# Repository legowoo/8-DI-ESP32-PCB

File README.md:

# 8-DI-ESP32-PCB
A printed circuit board that enables a ESP32 to interface with digital inputs up to 28VDC.

# Features
- 8 Galvanically isolated inputs
- Pluggable terminal blocks for connecting sensors
- Supports 12 and 24VDC sensors
- ESD protected inputs
- Reverse polarity protection
- Over current protection

# Technical Specification
- ESP32 Input voltage 5-16VDC
- Sensor Input voltage 5-28VDC (with 3/4W input resistors)
- Maximum input current draw 12mA
- Maximum board power draw ~10W

# Schematic

# How to use
- J9: Screw terminal for supplying voltage to the sensors that are connected to the optocouplers. Input voltage range: 5-24VDC
- J10: Screw terminal for supplying voltage to the ESP itself. Input voltage range: 5-12VDC

- D11: Led to indicate the presents/absent of a voltage on the VCC rail (J9).
- D12: Led to indicate the presents/absent of the +3V3 rail (J10).

- JP1: Jumper to connect the VCC to VPP. Used to remove the Galvanic isolation between the sensors and ESP.  
**Only populate this jumper if one voltage source is being used!**
- JP2: Jumper to connect GND1 to GND2. Used to remove the Galvanic isolation between the sensors and ESP.

- J1-J8: Each digital input has its own header connected to the ESP. Pinout from left to right: 1=VCC, 2=GND and 3=GPIO

- SW1: Resart the ESP
- SW2: put the ESP in program mode if the ESP is booting

- J11: Program connector. Connect any +3V3 UART programmer to write a program to the ESP.  
note: the ESP needs to be manualy set to program mode via SW1 and SW2.

# I/O mapping:  
- J1 -> GPIO36
- J2 -> GPIO39
- J3 -> GPIO34
- J4 -> GPIO35
- J5 -> GPIO19
- J6 -> GPIO21
- J7 -> GPIO22
- J8 -> GPIO23

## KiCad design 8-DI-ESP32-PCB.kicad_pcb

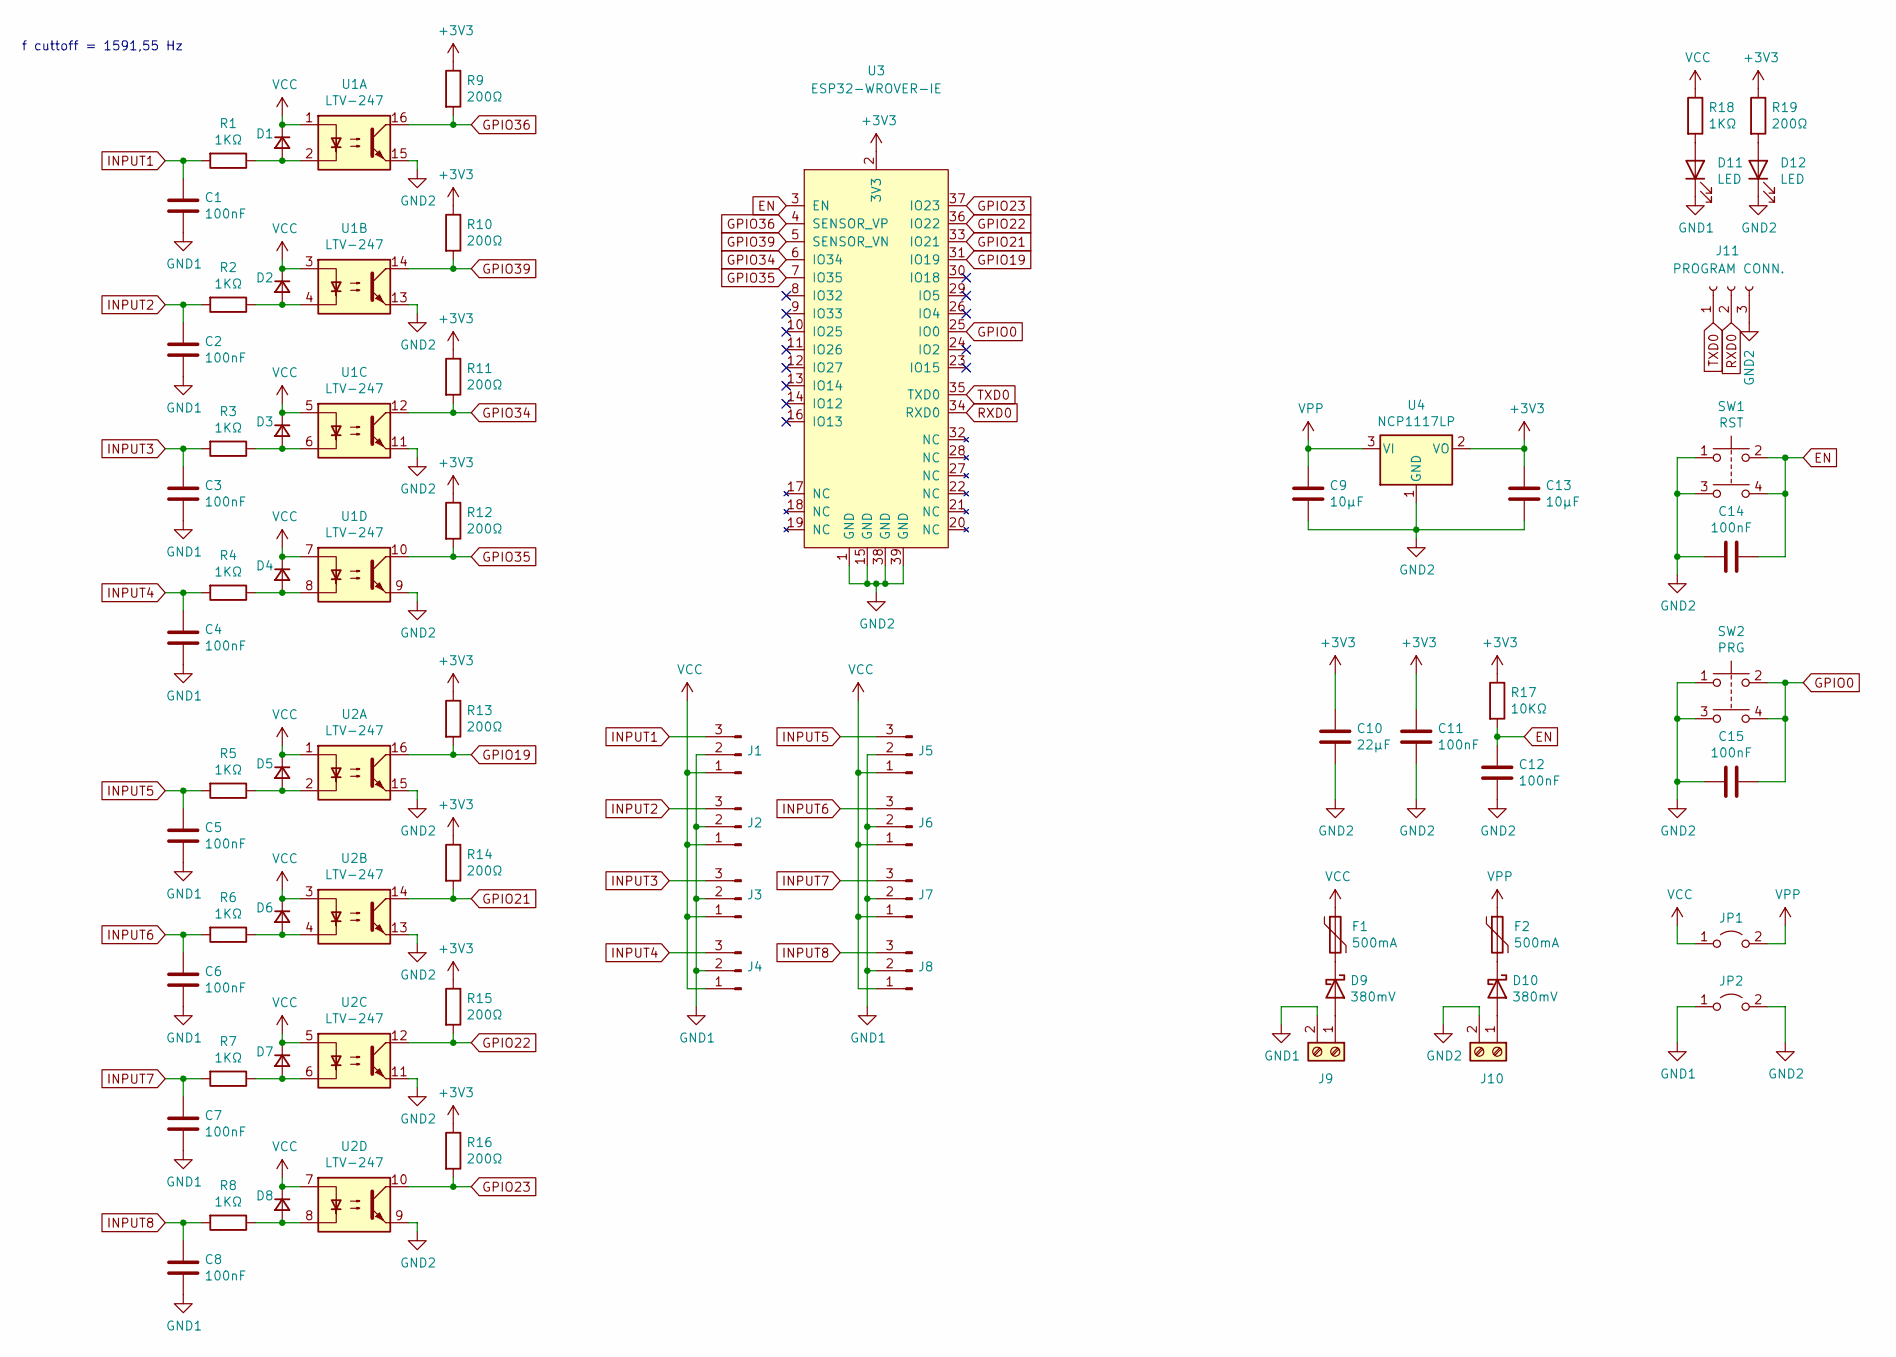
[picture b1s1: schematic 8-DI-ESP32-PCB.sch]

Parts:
C1, C2, C3, C4, C5, C6, C7, C8, C11, C12, C14, C15: 100nF; C_0805_2012Metric_Pad1.15x1.40mm_HandSolder; MPN 885012207098
C9, C13: 10µF; C_Elec_5x5.4; MPN 865080642006
C10: 22µF; C_Elec_6.3x5.4; MPN 865080643008
D1, D2, D3, D4, D5, D6, D7, D8: D_ESD; D_SOD-323_HandSoldering; MPN BAS21HT1G
D9, D10: 380mV; D_SOD-123F; MPN PMEG3005EGWX
D11, D12: LED; LED_1206_3216Metric; MPN 156120VS75000
F1, F2: 500mA; Fuse_1206_3216Metric_Pad1.42x1.75mm_HandSolder; MPN 0ZCJ0025AF2E
J1, J2, J3, J4, J5, J6, J7, J8: Conn_01x03_Male; CUI_TBP02R2-381-03BE; MPN TBP02R2-381-03BE
J9, J10: Screw_Terminal_01x02; CUI_TB004-508-02BE; MPN TB007-508-02BE
J11: PROGRAM CONN.; PinSocket_1x03_P2.54mm_Vertical
JP1, JP2: Jumper_2_Open; PinHeader_1x02_P2.54mm_Vertical
R1, R2, R3, R4, R5, R6, R7, R8, R18: 1KΩ; R_1206_3216Metric_Pad1.42x1.75mm_HandSolder; MPN RC1206FR-071KL
R9, R10, R11, R12, R13, R14, R15, R16, R19: 200Ω; R_1206_3216Metric_Pad1.42x1.75mm_HandSolder; MPN RC1206FR-07200RL
R17: 10KΩ; R_1206_3216Metric_Pad1.42x1.75mm_HandSolder; MPN RC1206FR-0710KL
SW1: RST; PTS647SM38SMTR2LFS; MPN PTS647SM38SMTR2LFS
SW2: PRG; PTS647SM38SMTR2LFS; MPN PTS647SM38SMTR2LFS
U1, U2: LTV-247; SOP-16_4.4x10.4mm_P1.27mm; MPN LTV-247
U3: ESP32-WROVER-IE; MPN M213EH2864UH3Q0
U4: NCP1117LP; SOT-223-3_TabPin2; MPN NCP1117LPST33T3G

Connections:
+3V3: C10.1, C11.1, C13.1, R9.1, R10.1, R11.1, R12.1, R13.1, R14.1, R15.1, R16.1, R17.1, R19.1, U3.2 (3V3), U4.2 (VO)
EN: C12.1, C14.1, R17.2, SW1.2, SW1.4, U3.3 (EN)
GND1: C1.2, C2.2, C3.2, C4.2, C5.2, C6.2, C7.2, C8.2, D11.1 (K), J1.2, J2.2, J3.2, J4.2, J5.2, J6.2, J7.2, J8.2, J9.2, JP2.1 (A)
GND2: C9.2, C10.2, C11.2, C12.2, C13.2, C14.2, C15.2, D12.1 (K), J10.2, J11.3, JP2.2 (B), SW1.1, SW1.3, SW2.1, SW2.3, U1.9, U1.11, U1.13, U1.15, U2.9, U2.11, U2.13, U2.15, U3.1 (GND), U3.15 (GND), U3.38 (GND), U3.39 (GND), U4.1 (GND)
GPIO0: C15.1, SW2.2, SW2.4, U3.25 (IO0)
GPIO19: R13.2, U2.16, U3.31 (IO19)
GPIO21: R14.2, U2.14, U3.33 (IO21)
GPIO22: R15.2, U2.12, U3.36 (IO22)
GPIO23: R16.2, U2.10, U3.37 (IO23)
GPIO34: R11.2, U1.12, U3.6 (IO34)
GPIO35: R12.2, U1.10, U3.7 (IO35)
GPIO36: R9.2, U1.16, U3.4 (SENSOR_VP)
GPIO39: R10.2, U1.14, U3.5 (SENSOR_VN)
INPUT1: C1.1, J1.3, R1.2
INPUT2: C2.1, J2.3, R2.2
INPUT3: C3.1, J3.3, R3.2
INPUT4: C4.1, J4.3, R4.2
INPUT5: C5.1, J5.3, R5.2
INPUT6: C6.1, J6.3, R6.2
INPUT7: C7.1, J7.3, R7.2
INPUT8: C8.1, J8.3, R8.2
unnamed: D1.2 (A), R1.1, U1.2
unnamed: D2.2 (A), R2.1, U1.4
unnamed: D3.2 (A), R3.1, U1.6
unnamed: D4.2 (A), R4.1, U1.8
unnamed: D5.2 (A), R5.1, U2.2
unnamed: D6.2 (A), R6.1, U2.4
unnamed: D7.2 (A), R7.1, U2.6
unnamed: D8.2 (A), R8.1, U2.8
unnamed: D9.1 (K), F1.2
unnamed: D9.2 (A), J9.1
unnamed: D10.1 (K), F2.2
unnamed: D10.2 (A), J10.1
unnamed: D11.2 (A), R18.2
unnamed: D12.2 (A), R19.2
RXD0: J11.2, U3.34 (RXD0)
TXD0: J11.1, U3.35 (TXD0)
VCC: D1.1 (K), D2.1 (K), D3.1 (K), D4.1 (K), D5.1 (K), D6.1 (K), D7.1 (K), D8.1 (K), F1.1, J1.1, J2.1, J3.1, J4.1, J5.1, J6.1, J7.1, J8.1, JP1.1 (A), R18.1, U1.1, U1.3, U1.5, U1.7, U2.1, U2.3, U2.5, U2.7
VPP: C9.1, F2.1, JP1.2 (B), U4.3 (VI)

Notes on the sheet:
f cuttoff = 1591,55 Hz

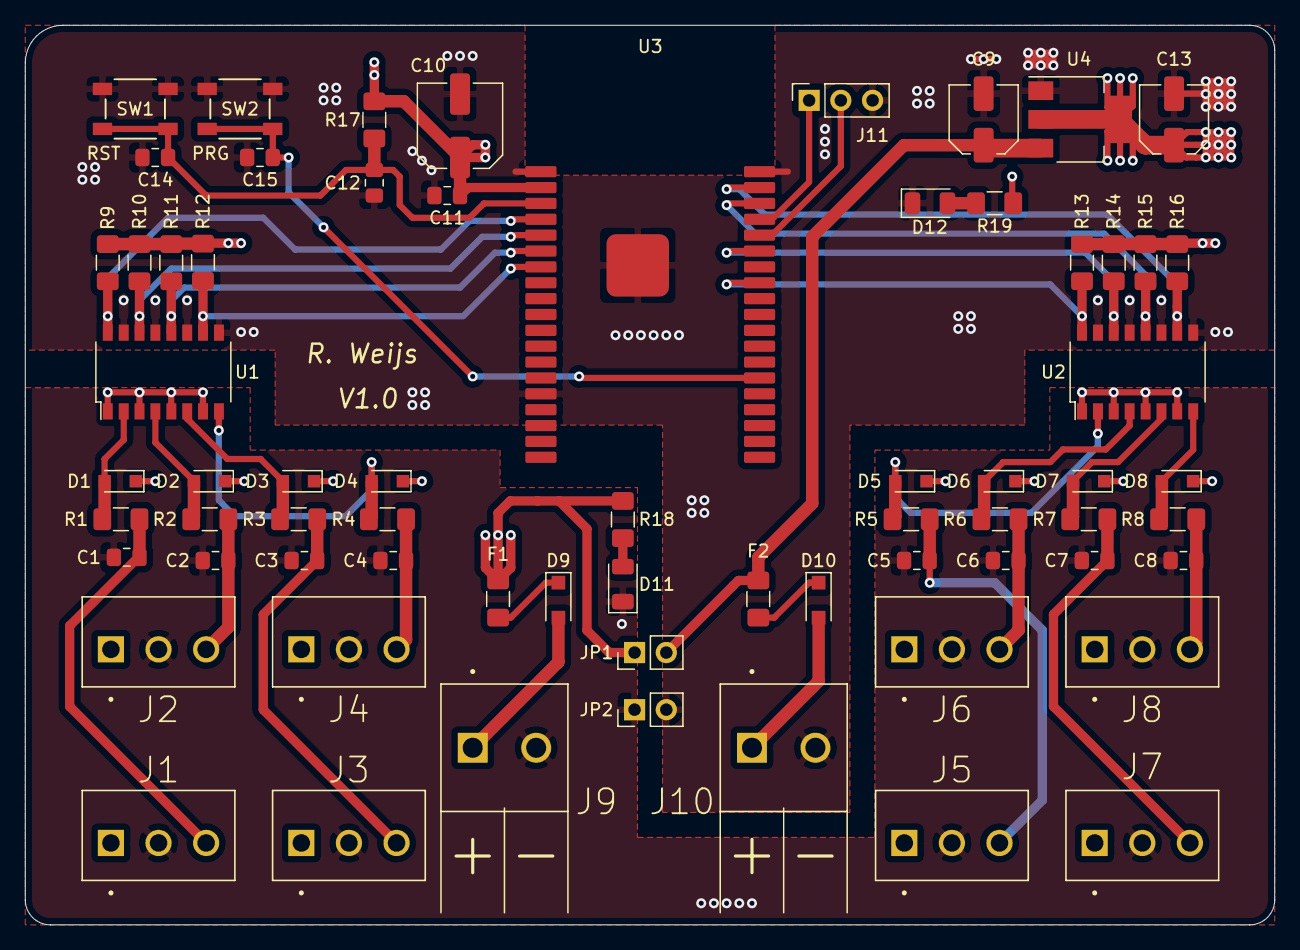
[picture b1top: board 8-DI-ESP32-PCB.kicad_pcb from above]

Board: 4 copper layers, 100.0 x 72.0 mm, 67 parts (0 on the bottom side), 39 nets.

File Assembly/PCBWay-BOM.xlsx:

|  |  | xxxx xxxx xxxxx xxPCS BOM
Item # | *Designator | *Qty | Manufacturer | *Mfg Part # | Description / Value | *Package/Footprint | Type | Your Instructions / Notes
1 | C9, C13 | 2 | Würth Elektronik | 865080642006 | Aluminum Electrolytic Capacitors 10uF, 50VDC, 20% | Capacitor 5x5.4mm | SMD
2 | C10 | 1 | Würth Elektronik | 865080643008 | Aluminum Electrolytic Capacitors 22uF, 50VDC, 20% | Capacitor 6.3x5.4mm | SMD
3 | C1-C8, C11, C12, C14 | 11 | Würth Elektronik | 885012207098 | MLCC X7R 0.1 uF, 50VDC, 10% | 0805 | SMD
4 | D1-D8 | 8 | ON Semiconductor | BAS21HT1G | General Purpose diode | SOD-323 | SMD
5 | D9, D10 | 2 | Nexperia | PMEG3005EGWX | Schottky Diodes, 380mV, 500mA | SOD-123 | SMD
6 | D11, D12 | 2 | Würth Elektronik | 156120VS75000 | Green LED, 2V, 20mA | 1206 | SMD
7 | F1, F2 | 2 | Bel Fuse | 0ZCJ0025AF2E | PPTC Fuse, 250mA hold, 500mA trip | 1206 | SMD
8 | J1-J8 | 8 | CUI Devices | TBP02R2-381-03BE | Terminal block, pluggable, P3.81mm, receptical, 3 poles | TerminalBlock 3 poles P3.81mm | thru-hole
9 | J9, J10 | 2 | CUI Devices | TB007-508-02BE | Terminal block, screw type, P5.08mm, 2 poles | TerminalBlock 2 poles P5.08mm | thru-hole
10 | J11 | 1 | *Generic* | / | General Purpose 1x03 pin socket P2.54 | PinSocket 1x03 P2.54mm | thru-hole
12 | R9-R16, R19 | 9 | Yageo | RC1206FR-07200RL | Resistors 200 OHM 1% 250mW | 1206 | SMD
13 | R17 | 1 | Yageo | RC1206FR-0710KL | Resistors 10K OHM 1% 250mW | 1206 | SMD
14 | R1-R8, R18 | 9 | Yageo | RC1206FR-071KL | Resistors 1K OHM 1% 250mW | 1206 | SMD
15 | SW1, SW2 | 2 | C&K | PTS647SM38SMTR2LFS | Tactile Switches, 1.8N 3.8mm H, G leads | Custom 4,5x4,5mm switch | SMD
16 | U1, U2 | 2 | Lite-On | LTV-247 | Transistor Output Optocouplers 4CH | SOP-16 P1.27mm | SMD
17 | U3 | 1 | Espressif Systems | M213EH6464UH3Q0 | ESP32-WROVER-IE, ESP32-D0WD-V3, 64Mbit PSRAM, 8 MB SPI flash, IPEX connector | ESP32-WROVER-IE | SMD | This is the version with 8 MB SPI flash
18 | U4 | 1 | ON Semiconductor | NCP1117LPST33T3G | 3.3V LDO Voltage Regulators | SOT-223-3 | SMD

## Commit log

2020-11-07 intial commit
2020-11-07 added readme
2020-11-07 clean-up temp. files
2020-11-07 Update README.md
    Update description
2020-12-07 added examples

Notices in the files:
parts and their libraries:
Copyright 2016 Accelerated Designs. All rights reserved.
